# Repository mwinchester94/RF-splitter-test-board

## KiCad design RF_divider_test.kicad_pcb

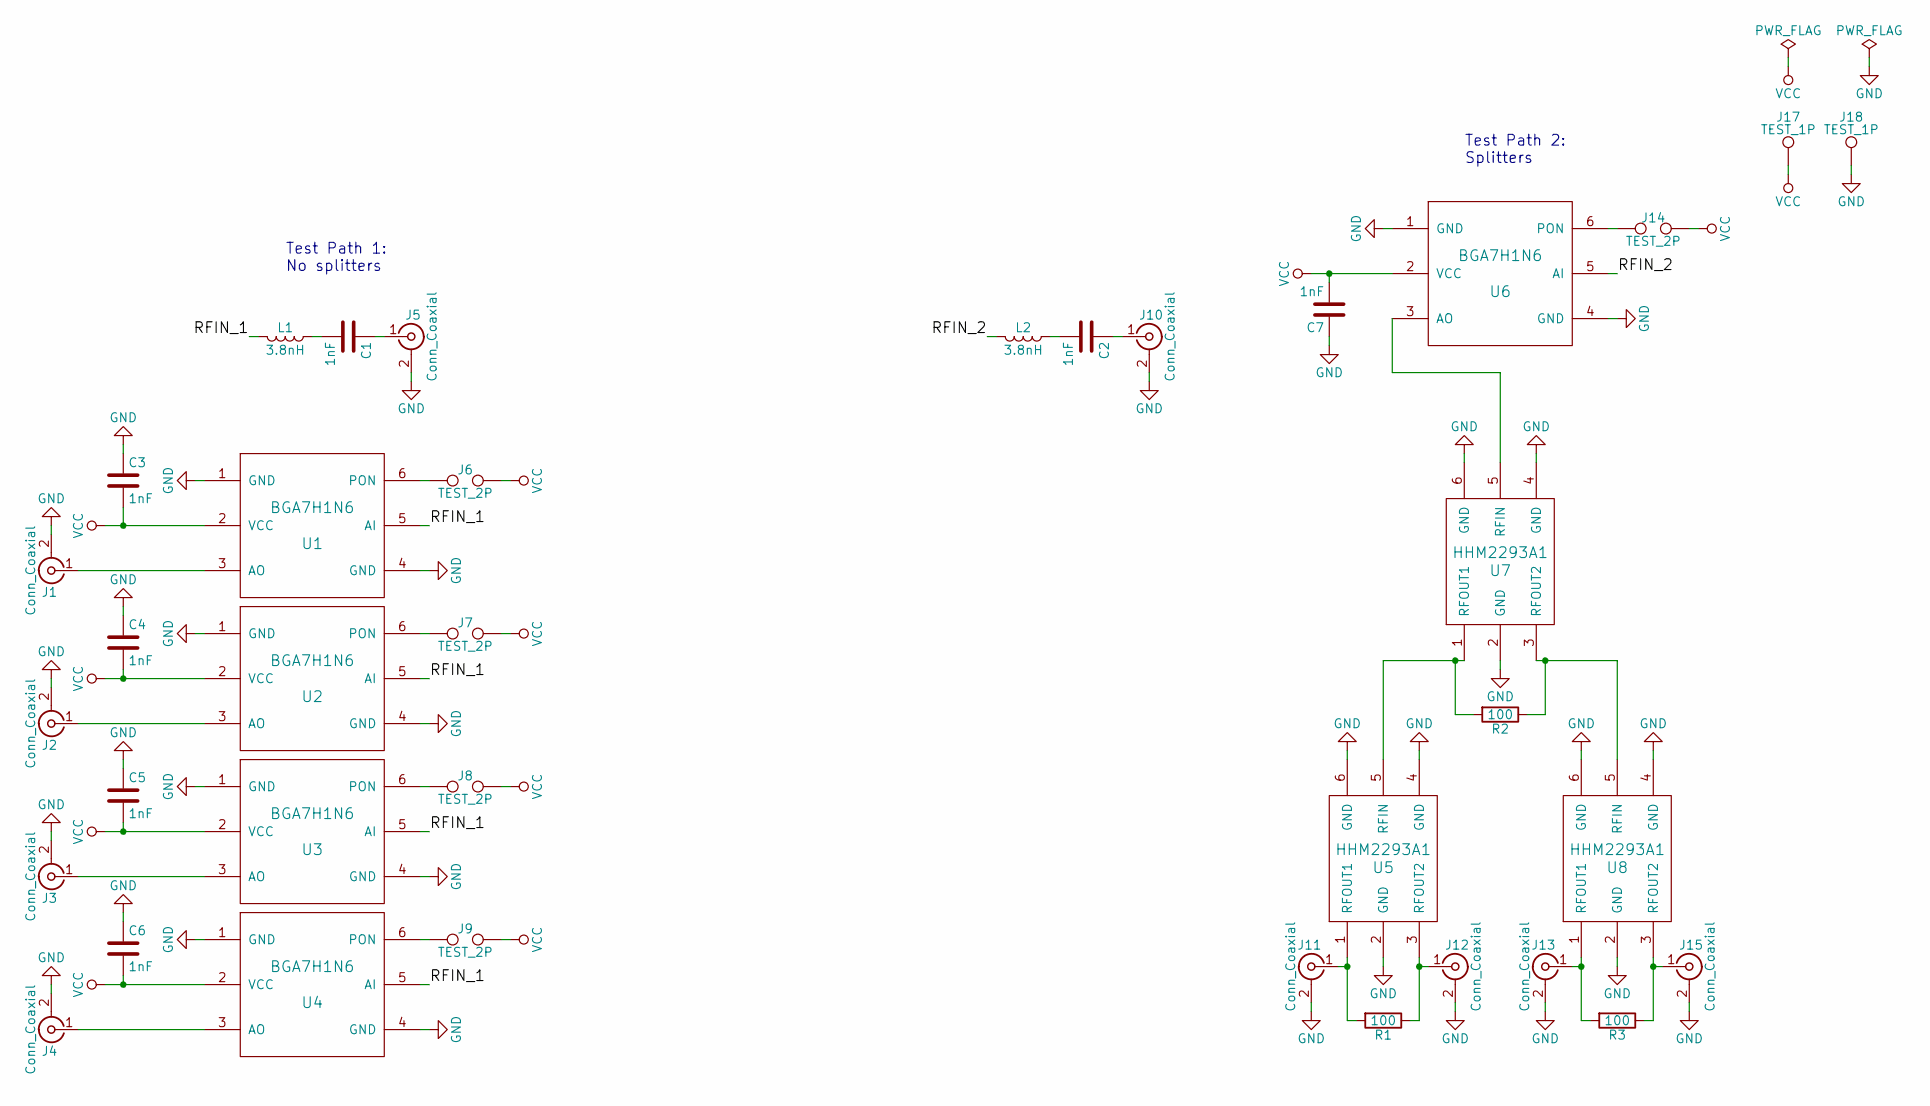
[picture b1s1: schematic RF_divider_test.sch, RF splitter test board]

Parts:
C1, C2, C3, C4, C5, C6, C7: 1nF; 0402
J1, J2, J3, J4, J5, J10, J11, J12, J13, J15: Conn_Coaxial; SMA-EDGE
J6, J7, J8, J9, J14: TEST_2P; 0603-JUMPER
J17, J18: TEST_1P; HEADER-1x1
L1, L2: 3.8nH; 0402
R1, R2, R3: 100; 0603
U1, U2, U3, U4, U6: BGA7H1N6; TSNP-6-2
U5, U7, U8: HHM2293A1

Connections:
/RFIN_1: L1.2, U1.5 (AI), U2.5 (AI), U3.5 (AI), U4.5 (AI)
/RFIN_2: L2.2, U6.5 (AI)
GND: C3.1, C4.1, C5.1, C6.1, C7.1, J1.2 (Ext), J2.2 (Ext), J3.2 (Ext), J4.2 (Ext), J5.2 (Ext), J10.2 (Ext), J11.2 (Ext), J12.2 (Ext), J13.2 (Ext), J15.2 (Ext), J18.1, U1.1 (GND), U1.4 (GND), U2.1 (GND), U2.4 (GND), U3.1 (GND), U3.4 (GND), U4.1 (GND), U4.4 (GND), U5.2 (GND), U5.4 (GND), U5.6 (GND), U6.1 (GND), U6.4 (GND), U7.2 (GND), U7.4 (GND), U7.6 (GND), U8.2 (GND), U8.4 (GND), U8.6 (GND)
unnamed: C1.1, J5.1 (In)
unnamed: C1.2, L1.1
unnamed: C2.1, J10.1 (In)
unnamed: C2.2, L2.1
unnamed: J1.1 (In), U1.3 (AO)
unnamed: J2.1 (In), U2.3 (AO)
unnamed: J3.1 (In), U3.3 (AO)
unnamed: J4.1 (In), U4.3 (AO)
unnamed: J6.1, U1.6 (PON)
unnamed: J7.1, U2.6 (PON)
unnamed: J8.1, U3.6 (PON)
unnamed: J9.1, U4.6 (PON)
unnamed: J11.1 (In), R1.2, U5.1 (RFOUT1)
unnamed: J12.1 (In), R1.1, U5.3 (RFOUT2)
unnamed: J13.1 (In), R3.2, U8.1 (RFOUT1)
unnamed: J14.1, U6.6 (PON)
unnamed: J15.1 (In), R3.1, U8.3 (RFOUT2)
unnamed: R2.1, U7.3 (RFOUT2), U8.5 (RFIN)
unnamed: R2.2, U5.5 (RFIN), U7.1 (RFOUT1)
unnamed: U6.3 (AO), U7.5 (RFIN)
VCC: C3.2, C4.2, C5.2, C6.2, C7.2, J6.2, J7.2, J8.2, J9.2, J14.2, J17.1, U1.2 (VCC), U2.2 (VCC), U3.2 (VCC), U4.2 (VCC), U6.2 (VCC)

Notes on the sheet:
Test Path 1: No splitters
Test Path 2: Splitters

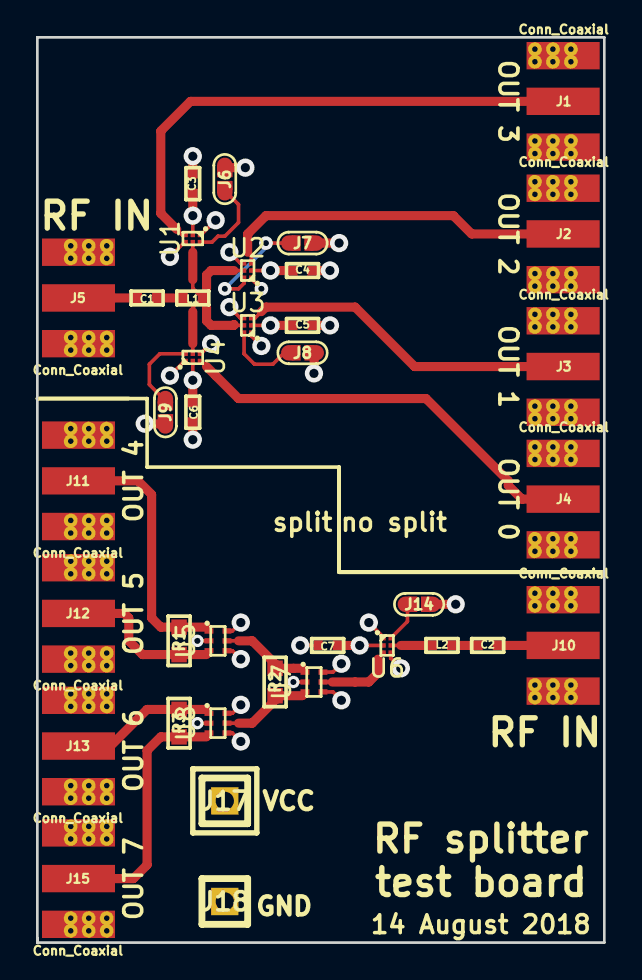
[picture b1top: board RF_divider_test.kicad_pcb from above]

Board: 4 copper layers, 31.5 x 50.3 mm, 37 parts (0 on the bottom side), 24 nets.

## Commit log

2018-08-14 Created RF splitter test schematic and PCB layout.
